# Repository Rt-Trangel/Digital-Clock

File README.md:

# Digital-Clock
A tiny digital clock with alarm clock and calendar function

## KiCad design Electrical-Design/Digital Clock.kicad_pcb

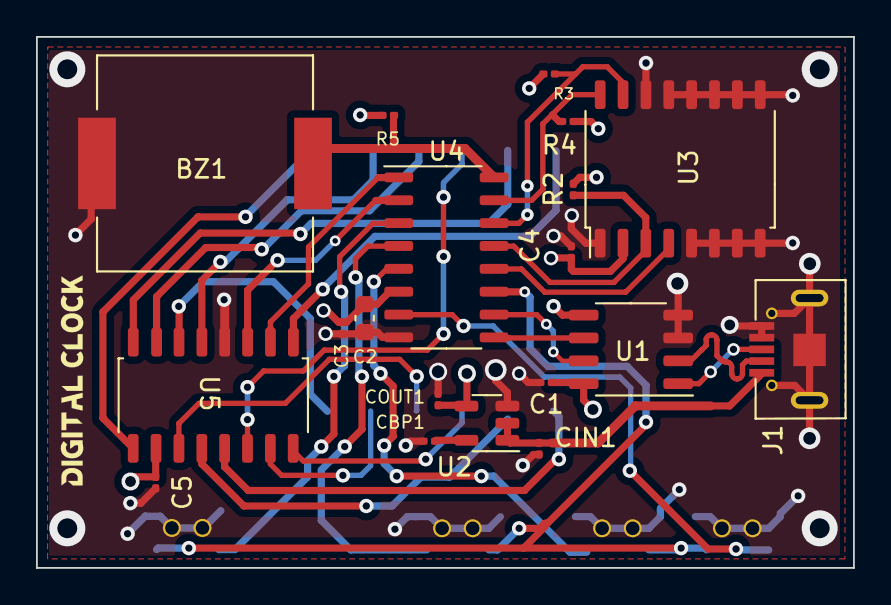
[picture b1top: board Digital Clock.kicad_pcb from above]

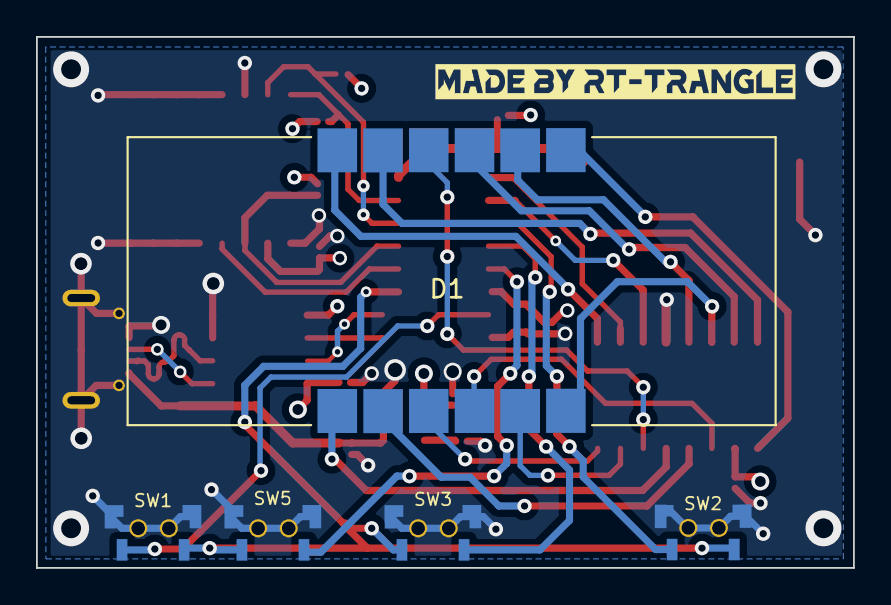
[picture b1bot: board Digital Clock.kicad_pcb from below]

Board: 4 copper layers, 45.4 x 29.5 mm, 26 parts (6 on the bottom side), 32 nets.

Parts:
BZ1: Buzzer; Buzzer1230
C1, C5: 104; C_0201_0603Metric
C2: 47uF; C_0603_1608Metric
C3: 0.1uF; C_0201_0603Metric
C4: 1uF; C_0201_0603Metric
CBP1: 0.01uF; C_0201_0603Metric
CIN1: 1uF; C_0201_0603Metric
COUT1: 1uF; C_0201_0603Metric
D1: Digital_tube
G1, G2: LOGO
J1: USB_B_Micro; USB
R2, R3, R4: 10K; R_0201_0603Metric
R5: 1650R; R_0201_0603Metric
SW1, SW2, SW3, SW5: SW_Push; Switch
U1: CH340N; SOP-8_3.9x4.9mm_P1.27mm
U2: SGM2028; SOT-23-5
U3: DS3231
U4: STC15W207S; STC_SOP-16_3.9x9.9mm_P1.27mm
U5: TM1650

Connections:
/A: D1.5 (A), U5.8 (A/KI1)
/B: D1.6 (B), U5.9 (B/KI2)
/C: D1.7 (C), U5.11 (C/KI3)
/D: D1.8 (D), U5.12 (D/KI4)
/DIG1: D1.1 (DIG1), U5.1 (DIG1)
/DIG2: D1.3 (DIG3), U5.5 (DIG2)
/DIG3: D1.4 (DIG4), U5.6 (DIG3)
/DIG4: D1.2 (DIG2), U5.7 (DIG4)
/DP: D1.12 (H), U5.16 (DP/KP)
/E: D1.9 (E), U5.13 (E/KI5)
/F: D1.10 (F), U5.14 (F/KI6)
/G: D1.11 (G), U5.15 (G/KI7)
/P1.0: R4.1, U3.16 (SCL), U4.15 (P1.0/RSTOUT_LOW)
/P1.1: BZ1.2 (+), R5.2, U4.16 (P1.1)
/P1.2: U4.1 (CMPO/T0/P1.2), U5.2 (SCL)
/P1.3: U4.2 (P1.3), U5.3 (SDA)
/P1.4: SW2.2, U4.3 (T0CLKO/P1.4)
/P1.5: SW3.2, U4.4 (P1.5)
/P3.2: SW1.2, SW2.1, SW3.1, SW5.1, U4.11 (P3.2/INT0)
/P3.3: U3.4 (~RST), U4.12 (P3.3/INT1)
/P3.7: R3.2, U3.15 (SDA), U4.14 (P3.7/~INT3/TXD_2)
/P5.4: SW5.2, U4.5 (CMP-/MCLKO/RST/P5.4)
/P5.5: SW1.1, U4.7 (CMP+/P5.5)
/RX: U1.6 (TXD), U4.9 (P3.0/RxD/~INT4/T2CLKO)
/TX: U1.7 (RXD), U4.10 (P3.1/TXD/T2)
/UD+: J1.3 (D+), U1.1 (UD+)
/UD-: J1.2 (D-), U1.2 (UD-)
/~INT2: R2.2, U3.3 (~INT/SQW), U4.13 (P3.6/~INT2/RXD_2)
GND: BZ1.1 (-), C1.2, C2.1, C3.1, C4.2, C5.2, CBP1.2, CIN1.1, COUT1.1, J1.4 (ID), J1.5 (GND), J1.6 (Shield), J1.7, J1.8, SW1.3, SW1.4, SW2.3, SW2.4, SW3.3, SW3.4, SW5.3, SW5.4, U1.3 (GND), U1.4 (RTS#), U2.3 (GND), U3.1 (32kHz), U3.5 (N.C.), U3.6 (N.C.), U3.7 (N.C.), U3.8 (N.C.), U3.9 (N.C.), U3.10 (N.C.), U3.11 (N.C.), U3.12 (N.C.), U3.13 (GND), U3.14 (VBAT), U4.8 (GND), U5.4 (GND)
unnamed: CBP1.1, U2.5 (BP)
unnamed: CIN1.2, J1.1 (VBUS), U2.1 (IN), U2.2 (EN)
VCC: C1.1, C2.2, C3.2, C4.1, C5.1, COUT1.2, R2.1, R3.1, R4.2, R5.1, U1.5 (VCC), U1.8 (V3), U2.4 (OUT), U3.2 (VCC), U4.6 (VCC), U5.10 (VDD)

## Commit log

2022-09-04 Create LICENSE
2022-09-04 Add Bill of Material
2022-09-04 Add package
2022-09-04 Add the document of the components used
2022-09-04 Add gerber
2022-09-04 Add schematic
2022-09-04 Something interesting!
2022-09-04 Add main files
